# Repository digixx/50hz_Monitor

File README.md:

# 50Hz Monitor
Monitoring the frequency of your main power.

The device is powered with 9V AC. The AC is converted with a full bridge rectifier producing positiv sinus cycles at 100 Hz rate.
A comparator generates interrupts on the ESP8266 MCU. A diode decouples the sinus from the following DC stage where 5V is generated.
 This drives the ESP and the LCD display. Timer1 is used to count a few sinus cycles and the MCU calculates the frequency.

The measured frequency is send periodically to a website for data storing and display the graph with RRD.

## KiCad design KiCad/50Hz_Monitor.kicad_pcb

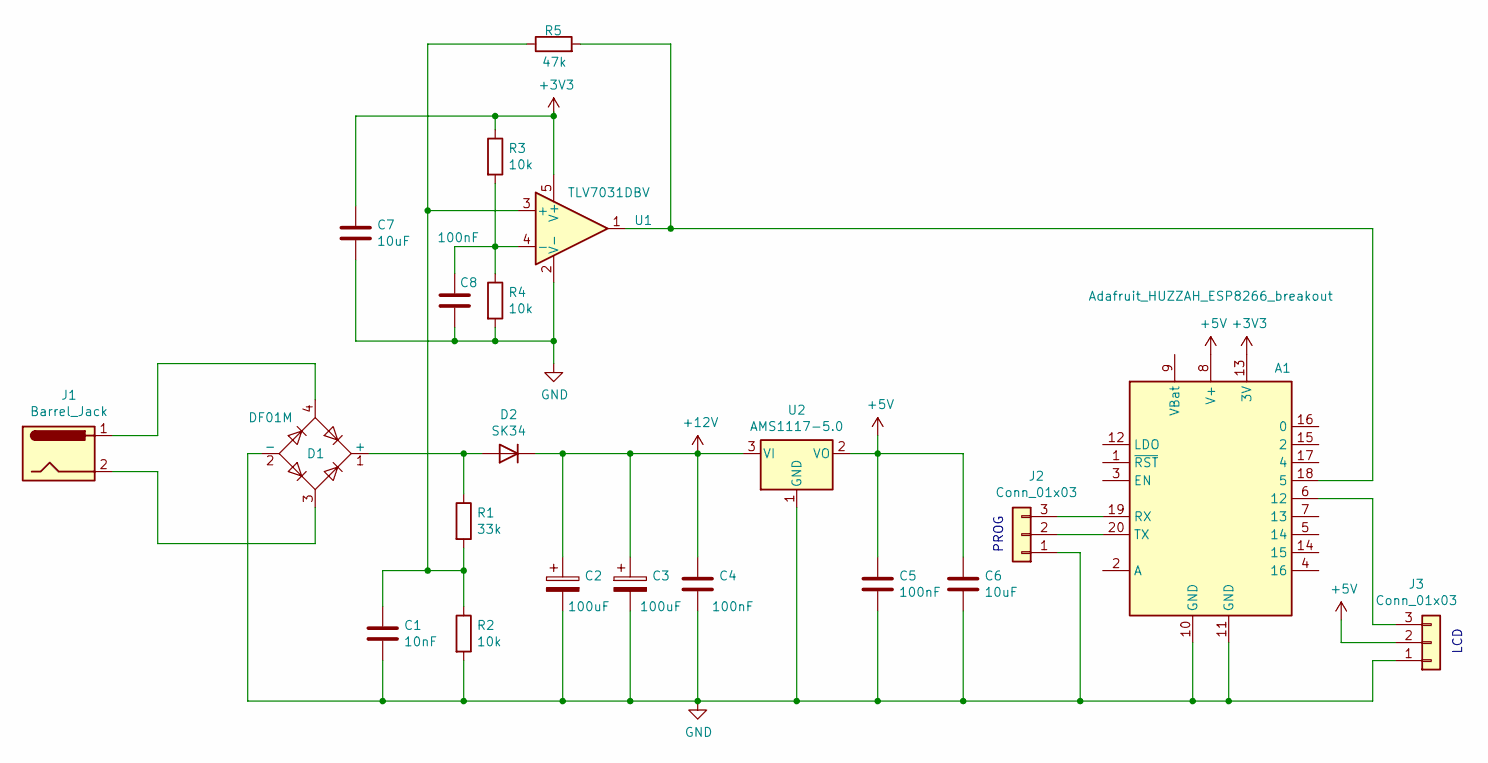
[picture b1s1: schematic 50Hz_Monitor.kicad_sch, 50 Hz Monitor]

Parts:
A1: Adafruit_HUZZAH_ESP8266_breakout
C1: 10nF; C_1206_3216Metric_Pad1.33x1.80mm_HandSolder
C2, C3: 100uF; CP_Radial_D7.5mm_P2.50mm
C4, C5, C8: 100nF; C_1206_3216Metric_Pad1.33x1.80mm_HandSolder
C6, C7: 10uF; C_1206_3216Metric_Pad1.33x1.80mm_HandSolder
D1: DF01M; Diode_Bridge_DIP-4_W7.62mm_P5.08mm
D2: SK34; D_SMA_Handsoldering
J1: Barrel_Jack; BarrelJack_Horizontal
J2, J3: Conn_01x03; PinHeader_1x03_P2.54mm_Vertical
R1: 33k; R_1206_3216Metric_Pad1.30x1.75mm_HandSolder
R2, R3, R4: 10k; R_1206_3216Metric_Pad1.30x1.75mm_HandSolder
R5: 47k; R_1206_3216Metric_Pad1.30x1.75mm_HandSolder
U1: TLV7031DBV; SOT-23-5
U2: AMS1117-5.0; SOT-223-3_TabPin2

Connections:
+3V3: A1.13 (3V), C7.1, R3.1, U1.5 (V+)
+5V: A1.8 (V+), C5.1, C6.1, J3.2, U2.2 (VO)
+12V: C2.1, C3.1, C4.1, D2.1 (K), U2.3 (VI)
GND: A1.10 (GND), A1.11 (GND), C1.2, C2.2, C3.2, C4.2, C5.2, C6.2, C7.2, C8.2, D1.2 (-), J2.1, J3.1, R2.2, R4.2, U1.2 (V-), U2.1 (GND)
unnamed: A1.6 (12), J3.3
unnamed: A1.18 (5), R5.2, U1.1
unnamed: A1.19 (RX), J2.3
unnamed: A1.20 (TX), J2.2
unnamed: C1.1, R1.2, R2.1, R5.1, U1.3 (+)
unnamed: C8.1, R3.2, R4.1, U1.4 (-)
unnamed: D1.1 (+), D2.2 (A), R1.1
unnamed: D1.3, J1.2
unnamed: D1.4, J1.1

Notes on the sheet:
LCD
PROG

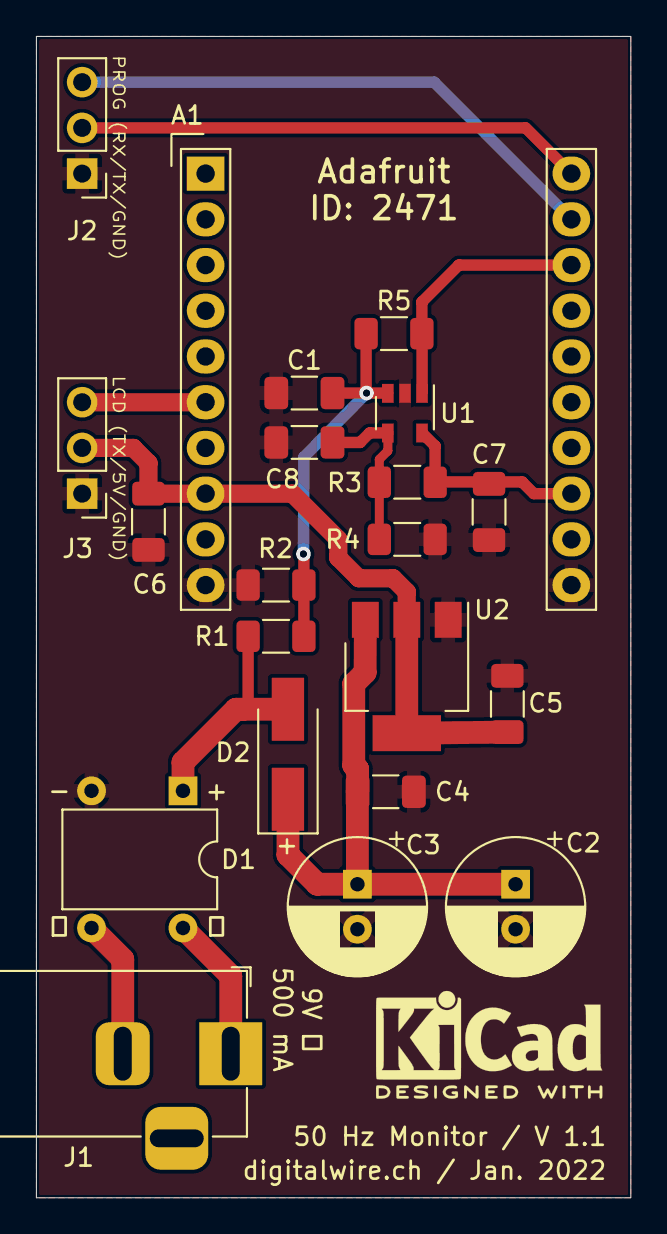
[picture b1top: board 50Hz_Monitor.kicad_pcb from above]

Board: 2 copper layers, 33.0 x 64.5 mm, 21 parts (0 on the bottom side), 13 nets.

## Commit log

2022-01-23 Initial release
2022-05-26 Code enhanced for multiple sensor data / housing added
